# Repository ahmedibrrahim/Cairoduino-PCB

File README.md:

Cairoduino Board Eagle project.

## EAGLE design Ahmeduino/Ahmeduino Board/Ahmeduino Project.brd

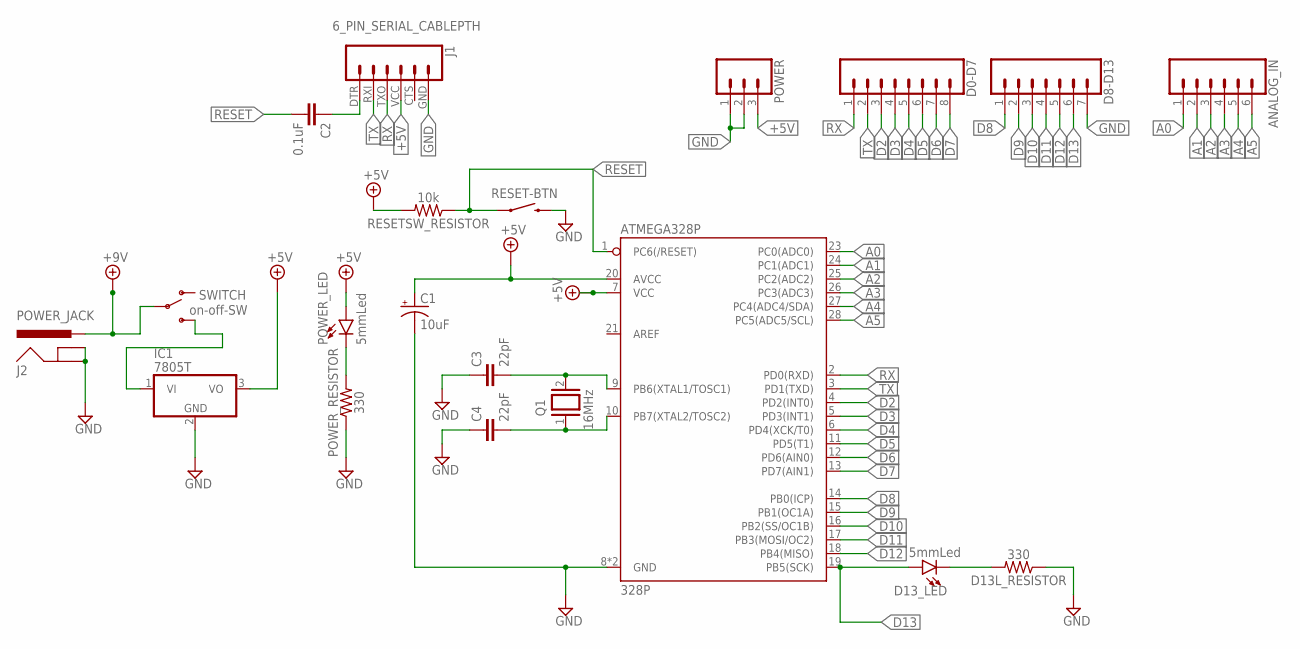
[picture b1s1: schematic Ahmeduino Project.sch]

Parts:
ANALOG_IN: CONN_06LONGPADS; 1X06_LONGPADS
ATMEGA328P: 328P; DIP28
C1: 10uF; CPOL-RADIAL-2.5MM-5MM
C2: 0.1uF; CAP-PTH-SMALL-KIT
C3, C4: 22pF; CAP-PTH-2.54
D0-D7: CONN_08LONGPADS; 1X08_LONGPADS
D8-D13: CONN_07LONGPADS; 1X07_LONGPADS
D13L_RESISTOR: 330; AXIAL-0.3
D13_LED: 5mmLed; LED_5MM
IC1: 7805T; TO220H
J1: 6_PIN_SERIAL_CABLEPTH; FTDI_BASIC
J2: POWER_JACK; POWER_JACK_PTH
POWER: CONN_03LONGPADS; 1X03_LONGPADS
POWER_LED: 5mmLed; LED_5MM
POWER_RESISTOR: 330; AXIAL-0.3
Q1: 16MHz; QS
RESET-BTN: ResetBtn; TACTILE_SWITCH_PTH_6.0MM
RESETSW_RESISTOR: 10k; AXIAL-0.3
SWITCH: on-off-SW; SWITCH_SPDT_PTH_11.6X4.0MM

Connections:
+5V: ATMEGA328P.7 (VCC), ATMEGA328P.20 (AVCC), C1.1 (+), IC1.3 (VO), J1.VCC (4), POWER.3, POWER_LED.A, RESETSW_RESISTOR.P$2 (2)
+9V: J2.PWR, SWITCH.2
A0: ANALOG_IN.1, ATMEGA328P.23 (PC0(ADC0))
A1: ANALOG_IN.2, ATMEGA328P.24 (PC1(ADC1))
A2: ANALOG_IN.3, ATMEGA328P.25 (PC2(ADC2))
A3: ANALOG_IN.4, ATMEGA328P.26 (PC3(ADC3))
A4: ANALOG_IN.5, ATMEGA328P.27 (PC4(ADC4/SDA))
A5: ANALOG_IN.6, ATMEGA328P.28 (PC5(ADC5/SCL))
D2: ATMEGA328P.4 (PD2(INT0)), D0-D7.3
D3: ATMEGA328P.5 (PD3(INT1)), D0-D7.4
D4: ATMEGA328P.6 (PD4(XCK/T0)), D0-D7.5
D5: ATMEGA328P.11 (PD5(T1)), D0-D7.6
D6: ATMEGA328P.12 (PD6(AIN0)), D0-D7.7
D7: ATMEGA328P.13 (PD7(AIN1)), D0-D7.8
D8: ATMEGA328P.14 (PB0(ICP)), D8-D13.1
D9: ATMEGA328P.15 (PB1(OC1A)), D8-D13.2
D10: ATMEGA328P.16 (PB2(SS/OC1B)), D8-D13.3
D11: ATMEGA328P.17 (PB3(MOSI/OC2)), D8-D13.4
D12: ATMEGA328P.18 (PB4(MISO)), D8-D13.5
D13: ATMEGA328P.19 (PB5(SCK)), D8-D13.6, D13_LED.A
GND: ATMEGA328P.8 (GND), ATMEGA328P.22 (GND), C1.2 (-), C3.1, C4.1, D8-D13.7, D13L_RESISTOR.P$1 (1), IC1.2 (GND), J1.GND (6), J2.GND, J2.GNDBREAK, POWER.1, POWER.2, POWER_RESISTOR.P$1 (1), RESET-BTN.3 (2)
unnamed: ATMEGA328P.9 (PB6(XTAL1/TOSC1)), C3.2, Q1.2
unnamed: ATMEGA328P.10 (PB7(XTAL2/TOSC2)), C4.2, Q1.1
unnamed: C2.1, J1.DTR (1)
unnamed: IC1.1 (VI), SWITCH.3 (S)
unnamed: POWER_LED.K (C), POWER_RESISTOR.P$2 (2)
unnamed: D13L_RESISTOR.P$2 (2), D13_LED.K (C)
RESET: ATMEGA328P.1 (PC6(/RESET)), C2.2, RESET-BTN.1, RESETSW_RESISTOR.P$1 (1)
RX: ATMEGA328P.2 (PD0(RXD)), D0-D7.1, J1.TXO (3)
TX: ATMEGA328P.3 (PD1(TXD)), D0-D7.2, J1.RXI (2)

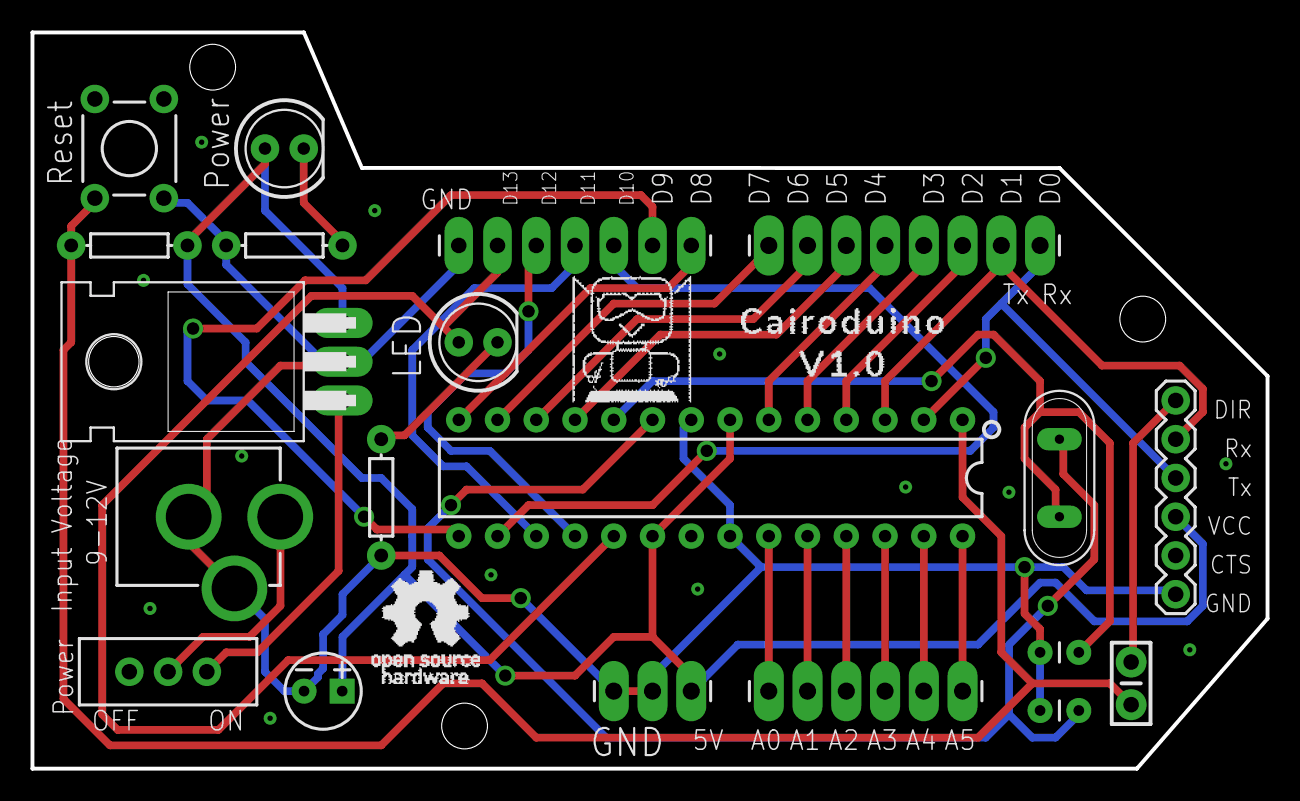
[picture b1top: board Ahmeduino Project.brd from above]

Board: 2 copper layers, 81.0 x 48.2 mm, 20 parts (0 on the bottom side), 30 nets.

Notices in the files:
parts and their libraries:
SparkFun-Connectors: Licensing: Creative Commons ShareAlike 4.0 International - https://creativecommons.org/licenses/by-sa/4.0
